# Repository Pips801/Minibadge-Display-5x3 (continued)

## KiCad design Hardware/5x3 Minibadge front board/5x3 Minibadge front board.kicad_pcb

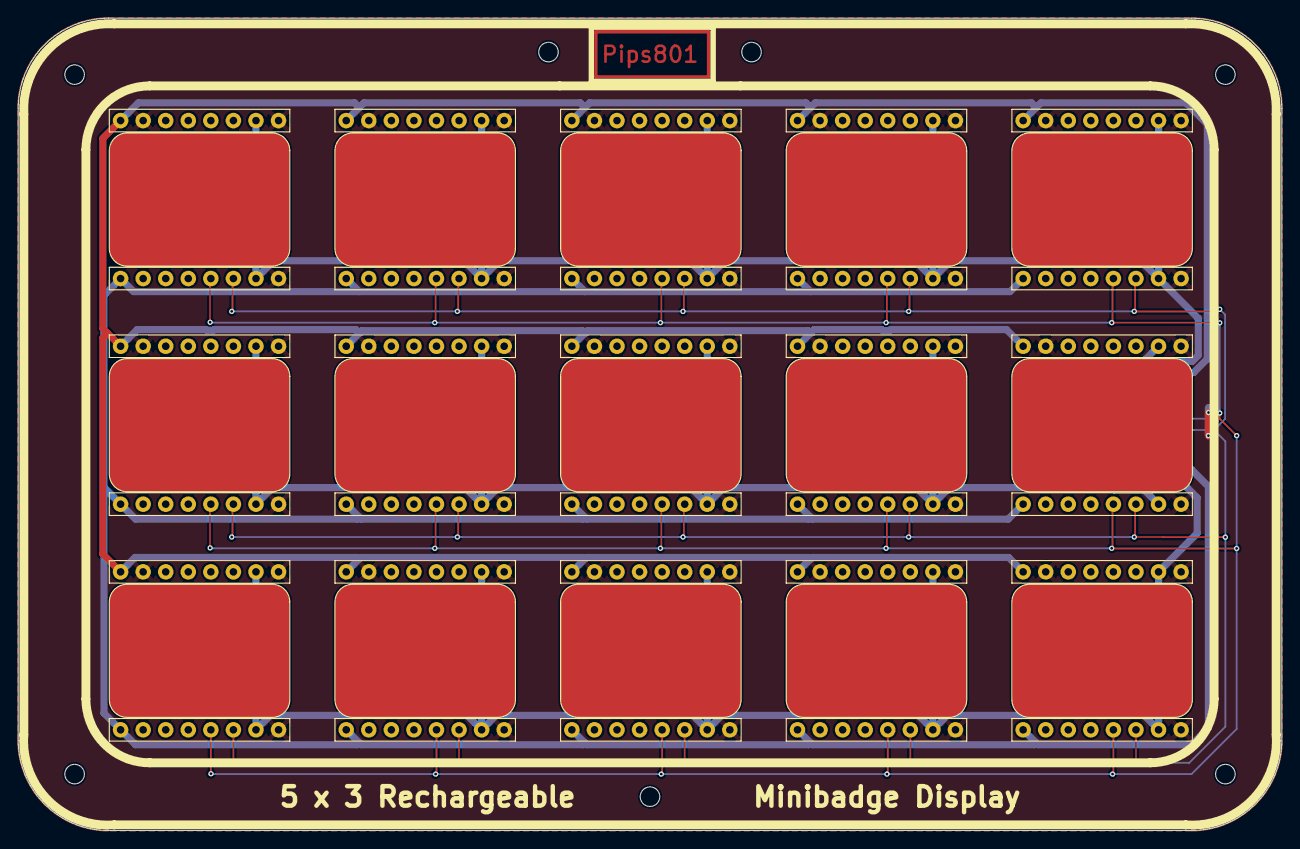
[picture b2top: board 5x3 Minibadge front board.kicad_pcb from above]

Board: 2 copper layers, 142.2 x 91.4 mm, 16 parts (1 on the bottom side), 8 nets.

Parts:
J1: Board to Board; PinHeader_2x05_P2.54mm_Vertical_SMD
MB1, MB2, MB3, MB4, MB5, MB6, MB7, MB8, MB9, MB10, MB11, MB12, MB13, MB14, MB15: MiniBadge_Full; MiniBadge_Slot_Reflective

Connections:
+3v3-1: J1.2, MB1.7 (+3V3), MB1.15 (3V3+), MB2.7 (+3V3), MB2.15 (3V3+), MB3.7 (+3V3), MB3.15 (3V3+), MB4.7 (+3V3), MB4.15 (3V3+), MB5.7 (+3V3), MB5.15 (3V3+)
+3v3-2: J1.1, MB6.7 (+3V3), MB6.15 (3V3+), MB7.7 (+3V3), MB7.15 (3V3+), MB8.7 (+3V3), MB8.15 (3V3+), MB9.7 (+3V3), MB9.15 (3V3+), MB10.7 (+3V3), MB10.15 (3V3+)
+3v3-3: J1.4, MB11.7 (+3V3), MB11.15 (3V3+), MB12.7 (+3V3), MB12.15 (3V3+), MB13.7 (+3V3), MB13.15 (3V3+), MB14.7 (+3V3), MB14.15 (3V3+), MB15.7 (+3V3), MB15.15 (3V3+)
+5V: J1.6, MB1.1 (+VBATT), MB2.1 (+VBATT), MB3.1 (+VBATT), MB4.1 (+VBATT), MB5.1 (+VBATT), MB6.1 (+VBATT), MB7.1 (+VBATT), MB8.1 (+VBATT), MB9.1 (+VBATT), MB10.1 (+VBATT), MB11.1 (+VBATT), MB12.1 (+VBATT), MB13.1 (+VBATT), MB14.1 (+VBATT), MB15.1 (+VBATT)
GND: J1.9, J1.10, MB1.2 (GND), MB1.8 (GND), MB1.16 (GND), MB2.2 (GND), MB2.8 (GND), MB2.16 (GND), MB3.2 (GND), MB3.8 (GND), MB3.16 (GND), MB4.2 (GND), MB4.8 (GND), MB4.16 (GND), MB5.2 (GND), MB5.8 (GND), MB5.16 (GND), MB6.2 (GND), MB6.8 (GND), MB6.16 (GND), MB7.2 (GND), MB7.8 (GND), MB7.16 (GND), MB8.2 (GND), MB8.8 (GND), MB8.16 (GND), MB9.2 (GND), MB9.8 (GND), MB9.16 (GND), MB10.2 (GND), MB10.8 (GND), MB10.16 (GND), MB11.2 (GND), MB11.8 (GND), MB11.16 (GND), MB12.2 (GND), MB12.8 (GND), MB12.16 (GND), MB13.2 (GND), MB13.8 (GND), MB13.16 (GND), MB14.2 (GND), MB14.8 (GND), MB14.16 (GND), MB15.2 (GND), MB15.8 (GND), MB15.16 (GND)
MB_CLK: J1.5, MB1.9 (CLK), MB2.9 (CLK), MB3.9 (CLK), MB4.9 (CLK), MB5.9 (CLK), MB6.9 (CLK), MB7.9 (CLK), MB8.9 (CLK), MB9.9 (CLK), MB10.9 (CLK), MB11.9 (CLK), MB12.9 (CLK), MB13.9 (CLK), MB14.9 (CLK), MB15.9 (CLK)
MB_SCL: J1.7, MB1.13 (SCL), MB2.13 (SCL), MB3.13 (SCL), MB4.13 (SCL), MB5.13 (SCL), MB6.13 (SCL), MB7.13 (SCL), MB8.13 (SCL), MB9.13 (SCL), MB10.13 (SCL), MB11.13 (SCL), MB12.13 (SCL), MB13.13 (SCL), MB14.13 (SCL), MB15.13 (SCL)
MB_SDA: J1.8, MB1.14 (SDA), MB2.14 (SDA), MB3.14 (SDA), MB4.14 (SDA), MB5.14 (SDA), MB6.14 (SDA), MB7.14 (SDA), MB8.14 (SDA), MB9.14 (SDA), MB10.14 (SDA), MB11.14 (SDA), MB12.14 (SDA), MB13.14 (SDA), MB14.14 (SDA), MB15.14 (SDA)

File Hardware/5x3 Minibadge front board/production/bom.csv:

Designator,Footprint,Quantity,Value,LCSC Part #
J1,PinHeader_2x05_P2.54mm_Vertical_SMD,1,Board to Board,
"MB1, MB10, MB11, MB12, MB13, MB14, MB15, MB2, MB3, MB4, MB5, MB6, MB7, MB8, MB9",MiniBadge_Slot_Reflective,15,MiniBadge_Full,

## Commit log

2025-01-14 Remove JLCPCB production output files
2025-01-15 flash + bms + usb switch
2025-01-15 lib-table
2025-01-15 BMS work
2025-01-15 rp2040 sub sheet
2025-01-17 more rp2040 work
    -BMS updates
    - rp2040 updates
    - add hardware design docs
2025-01-20 BMS updates
    - BMS mostly done
    - all BMS pins connected to RP2040
    - Re-did Minibadge pinouts
    - Connected RP2040 to USB Switch
2025-01-20 Add RP2040 Datasheet
2025-01-20 cleanup
2025-01-20 BMS updates
    Added missing capacitor for OTG
2025-01-20 Move to sub-folders
2025-01-20 Big changes
    - Folder changes
    - change dimensions of board to match thicker material
    - begin part selection/footprint selection
2025-01-20 Schematic changes
    - changed positions/schematic values and nets
2025-01-20 FIxing issues
    - Messed up mounting holes
    - board didn't copy to front plate
2025-01-21 Routed Minibadge Display
    god that sucked, and my routing sucks too.
2025-01-21 small chages
2025-01-21 Fix DRC errors
    got it down from 20+ Errors and 200+ warnings to zero errors and some unnecessary warnings!
2025-01-21 Add Voltage Regulators
    TLV1117LV33
2025-01-22 hardware changes and initial traces/layout
2025-01-22 Add Crystal
2025-01-22 1st semi complete board layout
2025-01-22 add JST connector
2025-01-22 Finish routing
2025-01-22 Forgot to route the TPM
2025-01-22 update power for TPM
2025-01-23 Add resistor for ILIM pin
2025-01-23 Diff Pair matching
    matched all USB lines to be within 1mm of length to each other
2025-01-23 more diff pair matching, fixed BMD Data lines
2025-01-23 add battery label
2025-01-23 Link USB-C port 3d model
2025-01-23 Change board size + mounting holes
    still need to finish re-routing the front plate
2025-01-23 physical changes
2025-01-23 re-routed front minibadge board
2025-01-23 remove wrong files
2025-01-23 front board initial silkscreen
2025-01-23 Silkscreen updates
2025-01-23 Part selection
2025-01-23 Swap 260Ω footprint for 0805
2025-01-23 R2 production files
2025-01-23 front plate production files
2025-01-24 Fixed BMS_STAT pin
2025-01-24 Fix BMS_STAT pin
    swapped RP2040 footprint for one with thermal vias
2025-01-25 Fix typo
2025-01-26 Reworking BMS
2025-01-27 refactor BMD schematic
2025-01-27 complete BMS layout
2025-01-27 Update GND symbols
2025-01-28 refactor PCB for new BMS layout
2025-01-29 All components routed
    - broke out resistor network into individual resistors
    - AGND tied to PGND by BMS
    - repositioned GPIO positions
    - length-matched USB to within 0.1mm
2025-01-29 debug pins for RP2040
2025-01-29 Add TagConnect SWD
2025-01-29 add PawConnect
2025-01-29 minor route changes
2025-01-29 GND stitching/thermal relief for voltage regulators
2025-01-29 Via stitching
2025-01-29 Update JST to white
2025-01-29 update 3d models
2025-01-29 swap PawConnect header
2025-01-29 Swap PawConnect side
2025-01-29 Initial graphics update
2025-01-29 Add button and LEDs
2025-01-30 Route 8x WS2812B-2020 LEDs
2025-01-30 measurments
2025-01-30 move debug header
2025-01-30 Silkscreen sectioning
2025-01-30 remove unused traces
2025-01-30 update constraints
2025-01-30 fix nets
2025-01-30 add caps for LEDs
2025-01-30 Pass DRC, updated for JLC capabilities
2025-01-30 update 0.1uf caps to 0402
2025-01-30 more silkscreen graphics
2025-01-30 update footprints
2025-01-30 adjust ground pours
2025-01-30 more silkscreen updates
2025-01-30 bump to R4
2025-01-30 swap diode footprint + add new part numbers
2025-01-30 update ILIM resistor for 250ohm
2025-01-30 Exclude BMS Reset from BOM
2025-01-30 Update gitignore
2025-01-30 add BOMs
2025-01-30 updated production files
2025-01-30 fix ohm s ymbol
2025-01-30 USB length matching
2025-01-30 adjust ground plane
2025-01-30 add Wh capacity + swap pawprints
2025-01-30 update planes
